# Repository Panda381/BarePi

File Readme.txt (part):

BarePi - Modular microchip kit
==============================
Last Update: 07/18/2026
Copyright (c) 2026 Miroslav Nemecek

Panda38@seznam.cz
hardyplotter2@gmail.com
https://github.com/Panda381/BarePi
https://www.breatharian.eu/hw/barepi/index_en.html

Note: The schematics and PCBs are in KiCAD version 9 format. The PCBs were
originally designed for home production using photolithography and may not be
properly prepared for professional production. If you want to have your PCBs
professionally produced, I recommend checking the designs carefully, especially
the dimensions of the components, which may not be correctly defined.
Typically, SMD capacitors may not have the correct dimensions.

Note 2: A WCH-LinkE programmer (available e.g. here
https://pajenicko.cz/usb-programator-a-debug-adapter-wch-link) may be required
to program CH32xxx processors. Before using it for the first time, it may be
necessary to upgrade the firmware of the programmer first - this can be done in
the MounRiver Studio development environment.

License
-------
All of my software creations are distributed under the Unlicense
https://spdx.org/licenses/Unlicense.html,
and my hardware creations under the CC0 license
https://creativecommons.org/publicdomain/zero/1.0/legalcode.en.
You are free to use, modify, and distribute them for any purpose without having
to credit me as the author. The exception is content derived from third-party
sources. These third-party components are not covered by my Unlicense or CC0
licenses, but rather by the original license terms of their authors. These
components are marked in the code, and when using them, you must comply with
the terms of the original licenses.

Contents
--------
- Description of the kit (basic characteristics of the kit)
- Bus connector (description of signals on the bus connector)
- Display connector (description of signals on the display connector)
- ZeroTiny (example of a minimalist game console with a Raspberry Zero module,
  created based on kit modules)
- EEPROM and driver formats (structure of EEPROMs and Register-Controlled
  Drivers)

Special modules
- Base (basic module - USB power supply, 3.3V stabilizer, audio output, microSD
  card, Reset button)
- BusExp (bus expander for connecting 4 modules)
- Port (ports SPI, I2C, UART, digital I/O, ADC)
- RTC (real-time clock and EEPROM memory)
- TestLed (bus tester)

Processors
- MegaTinyJoypad (Mega Tiny Joypad game console, ESP-07S processor module,
  128x64 OLED display)
- PGA2350 (PicoPadPGA game console, RP2350 processor)
- PicoPad (PicoPad console, RP2040 or RP2350 processor)
- PicoPadHSTX (PicoPadHSTX console with VGA or HDMI output, RP2350 processor)
- PidiBoy (PidiBoy console, CH32V006F8P6 processor, 128x64 OLED display)
- PidiMet, PidiMetAdapter (universal multimeter)
- PidiPad (PidiPad console, CH32V006E8R6 processor, output to VGA monitor)
- SumoPad (SumoPad console, CH32V208RBT6 processor, output to VGA monitor or
  LCD display 320x240)
- TinyJoypad (Tiny Joypad game console, ATtiny85 processor, 128x64 OLED
  display)
- TweetyBoy (TweetyBoy game console, CH32X035G8R6 processor, 160x80 LCD
  display)
- Zero (Raspberry Zero 1 or Raspberry Zero 2 module)

Displays
- DispHDMI (adapter for connecting an HDMI monitor)
- DispVGA (adapter for connecting a VGA monitor)
- ExtDisp (converter for grabbing a 320x240 LCD display and displaying it on a
  VGA or HDMI monitor)
- LCD16x2 (text LCD display, 2 rows of 16 characters)
- LCD160x80 (LCD color display 160x80)
- LCD320x240 (LCD color display 320x240)
- LED12 (7-segment LED display with 12 positions)
- OLED128x64 (OLED black and white display 128x64)

Keyboard
- CalcKey (calculator keyboard)
- KeyPad (basic gaming keyboard with 9 buttons)
- MiniKey (minimalist alphanumeric keyboard)

Description of the kit
----------------------
BarePi is a modular microchip kit designed for programming small devices such
as game consoles or calculators. The main focus is on the Raspberry Zero 2
module, programmed as bare-metal (i.e. without an operating system) with
library PiLibSDK (link www https://www.breatharian.eu/hw/pilibsdk/index_en.html,
GitHub https://github.com/Panda381/PiLibSDK). However, other types of
processors supporting 3.3V signals can also be used (ATmega, CH32V, ESP32).
The modules of the kit are connected via 40-pin connectors, forming a bus with
signals defined according to the Raspberry Zero 2 module. The connectors
ensure sufficient connection strength, no additional mechanical connections
are needed. Most modules are pass-through - they contain both a bus input
connector on the top edge of the board and a bus output connector on the
bottom edge of the board. The exceptions are the processor modules, which
contain only an output connector, and the alphanumeric keyboard module, which
has only an input connector.

The connection connector consists of a 2x20-pin female header on the bottom of
the module (signal output from the module - e.g. processor module) and a
2x20-pin pin header on the top of the module (signal input to the module - e.g.
keyboard). Most modules have a width of 65 millimeters, based on the width of
the Raspberry Zero 2 module. Most devices contain a processor module, a "Base"
module with power supply and sound output, a display module and a keyboard
module. All signals on the bus are at 3.3V levels. The bus also contains a 5V
supply voltage, but this voltage is used both to supply power to the device
(followed by a 3.3V stabilizer) and as a voltage for a possible signal
converter to the 5V level. The 5V level must not be applied to the signal wires
themselves, in many cases this could damage the device.

When building modules, you can solder the processor and display modules hard
over the pin strip, but I recommend using a socket strip for easy replacement.
The kit modules can be used in the simplest form, just the printed circuit
board itself, but it is more luxurious to add a top panel. For some modules,
such as the keyboard, the top panel is necessary because of the key labels. An
additional printed circuit board can be used as the top panel, screwed to the
module using spacers. The materials also include graphics for the bottom panel,
but it is probably unnecessary - the bottom side of the module can be treated,
for example, by gluing foam strips from window insulation so that the bottom
side of the printed circuit board does not scratch the table. For the kit
prototypes, instead of the top panel, I used only printed cardboard paper,
covered with insulating tape against abrasion and with holes punched with a
leather punch. For keyboards, I recommend adjusting the height of the keys so
that the keycaps protrude 1 mm above the surface of the top panel. If the
protrusion is too large, the keys may press into your fingers when pressed, and
if the protrusion is too small, more force may be required to press.

Bus connector
-------------
Definition of the signals on the bus connector, looking at the header strip on
the bottom edge of the module. The corresponding GPIO pin number of the
Raspberry Zero 2 module is shown in parentheses.

1,2 5V ... Supply voltage 5V. It is used to power the device, e.g. from a USB
connector or a 3.7V battery. The device itself is powered by a voltage of 3.3V,
so the device must also include a voltage stabilizer for 3.3V. All signals on
the bus are at 3.3V levels. If signals with a 5V level are needed, a level
converter must be used.

3,4 3V3 ... Supply voltage 3.3V. This is the main supply voltage of the device.
It can be obtained by a stabilizer from a 5V voltage (e.g. from a USB
connector) or a voltage converter from a battery.

5 BUS_SDA (GPIO0) ... Internal I2C bus data wire. The internal I2C bus is used
to directly control the modules of the kit. The internal I2C bus can be a
separate bus, separated from the external user I2C bus, so that the user can
independently control the communication. In the Raspberry Zero 2 module, this
is the I2C0 bus. In other modules, the internal I2C bus can be shared with the
external I2C bus. In the Raspberry Zero 2 module, the I2C0 bus is also used to
access the system ID EEPROM memory when the device is turned on - this must be
remembered to avoid overlapping the functions of the EEPROM memory. The signal
is of the open collector type - pull-up resistors must be used.

6 BUS_SCL (GPIO1) ... Clock wire of the internal I2C bus. In the Raspberry
Zero 2 module this is the I2C0 bus. The signal is of the open collector type -
pull-up resistors must be used.

7 I2C_SDA (GPIO2) ... External I2C bus data wire. The external I2C bus is used
to control user devices so that communication does not conflict with the
control of the kit modules. In the Raspberry Zero 2 module, this is the I2C1
bus. In other modules, the external I2C bus may be shared with the internal I2C
bus. The signal is of the open collector type - pull-up resistors must be used.

8 I2C_SCL (GPIO3) ... Clock wire of external I2C bus. In Raspberry Zero 2
module this is I2C1 bus. Signal is open collector type - pull-up resistors must
be used.

9 KEY_ALT (GPIO4) ... Input of the alternative function button "ALT". The
button changes the meaning of the other keyboard keys. The button connects the
pin to GND and requires the use of a pull-up resistor. This signal can also
have other functions if the button function is not used. The clock signal from
the processor can be output to the pin - in the Raspberry Zero 2 module this is
the GPCLK0 signal. For this reason, the "ALT" button should be connected via a
protective resistor (e.g. 1K0), which will prevent damage to the circuits if
the button is accidentally pressed if the clock signal is output to the pin.
Another additional function of the pin is the input of the ADC converter -
typically in the Raspberry Pico and CH32 modules.

10 KEY_DOWN (GPIO5) ... "DOWN" button input. Along with the "ALT" button, it
has an alternative meaning of "Page Down". The button connects the pin to GND
and requires the use of a pull-up resistor.

11 KEY_UP (GPIO6) ... "UP" button input. Along with the "ALT" button, it has an
alternative meaning of "Page Up". The button connects the pin to GND and
requires the use of a pull-up resistor.

12 SPI_CS1 (GPIO7) ... The second SPI bus select signal. In the Raspberry Zero
module, this is the SPI0 bus.

13 SPI_CS0 (GPIO8) ... The first SPI bus select signal. In the Raspberry Zero
module, this is the SPI0 bus.

14 SPI_MISO (GPIO9) ... SPI bus MISO signal - data input to the processor from
the peripheral (RX signal). In the Raspberry Zero module, this is the SPI0 bus.
In some devices, the SPI bus may be shared with the SD card - in this case, it
is necessary to remove the SD card from the slot before using the SPI bus.

15 SPI_MOSI (GPIO10) ... SPI bus MOSI signal - data output from the processor
to the peripheral (TX signal). In the Raspberry Zero module, this is the SPI0
bus.

16 SPI_SCLK (GPIO11) ... SPI bus clock signal. In the Raspberry Zero module,
this is the SPI0 bus.

17 PWM_L (GPIO12) ... Left channel audio output. Typically PWM modulation, so
an RC filter may be required.

18 PWM_R (GPIO13) ... Right channel audio output. Typically PWM modulation, so
an RC filter may be required.

19 UART_TX (GPIO14) ... Serial data output of the UART port. In some modules,
this pin can be used as a CAN Bus serial data output (CAN_TX signal).

20 UART_RX (GPIO15) ... Serial data input of the UART port. In some modules,
this pin can be used as a CAN Bus serial data input (CAN_RX signal).

21 LCD_DC (GPIO16) ... Control signal for LCD SPI display - resolution of data
and control code.

22 LCD_RES (GPIO17) ... Signal to reset the LCD SPI display controller.

23 LCD_CS (GPIO18) ... Signal for selecting the LCD SPI display. In the
Raspberry Zero module, this is the SPI1 bus. The PCM_CLK signal for the I2S/PCM
interface can optionally be available on this pin.

24 LCD_BL (GPIO19) ... Signal for controlling the brightness of the LCD SPI
display backlight. Typically, this is a PWM signal. Optionally, the PCM_FS
signal for the I2S/PCM interface can be available on this pin. If the processor
does not allow smooth brightness control, this pin should be HIGH for full
display brightness.

25 LCD_MOSI (GPIO20) ... Serial data output to the LCD SPI display. In the
Raspberry Zero module, this is the SPI1 bus. The PCM_DIN signal for the I2S/PCM
interface can optionally be available on this pin.

26 LCD_SCK (GPIO21) ... LCD SPI display clock signal. In the Raspberry Zero
module, this is the SPI1 bus. Optionally, the PCM_DOUT signal for the I2S/PCM
interface can be available on this pin.

27 KEY_A (GPIO22) ... Input button "A" - the main action button. On the
alphanumeric keyboard, it corresponds to the "Spacebar" key. Together with the
"ALT" button, it has an alternative meaning of "Zoom" - switching the view on
the built-in LCD display. The button connects the pin to GND and requires the
use of a pull-up resistor.

28 KEY_B (GPIO23) ... "B" button input - secondary action button. On an
alphanumeric keyboard, it corresponds to the "Enter" key. Together with the
"ALT" button, it has an alternative meaning of "Insert". The button connects
the pin to GND and requires the use of a pull-up resistor.

29 KEY_X (GPIO24) ... Input button "X" - additional functions button (e.g.
help). On the alphanumeric keyboard it corresponds to the "Tab" key. Together
with the "ALT" button it has an alternative meaning "Print Screen" - screenshot
of the screen contents to a file. The button connects the pin to GND and
requires the use of a pull-up resistor.

30 KEY_RIGHT (GPIO25) ... "RIGHT" button input. Along with the "ALT" button, it
has an alternative meaning of "End". The button connects the pin to GND and
requires the use of a pull-up resistor.

31 KEY_LEFT (GPIO26) ... "LEFT" button input. Along with the "ALT" button, it
has an alternative meaning of "Home". The button connects the pin to GND and
requires the use of a pull-up resistor.

32 KEY_Y (GPIO27) ... "Y" button input - interrupt, exit or menu button. On an
alphanumeric keyboard, it corresponds to the "Esc" key. Together with the "ALT"
button, it has an alternative meaning of "Menu", invoking the system menu. The
button connects the pin to GND and requires the use of a pull-up resistor.

33 SD_CS ... SPI signal for selecting the SD card. An LED indicating access to
the SD card can be connected to this signal.

34 SD_MISO ... SPI data input from SD card to processor.

35 SD_MOSI ... SPI data output from the processor to the SD card.

36 SD_SCLK ... SPI clock for SD card.

37 USR_LED ... Output to user LED. Active signal is HIGH.

38 RESET ... "RESET" button input for resetting the processor. The button
connects the pin to GND and requires the use of a pull-up resistor. For some
modules, the pull-up resistor is internally part of the module.

39, 40 GND ... Ground 0V.

In most modules, the I2C bus signals are equipped with a 15K pull-up resistor.
This value should ensure reliable bus operation with 1 to 5 connected devices.
The BarePi kit modules use the following I2C addresses:
0x30 ... LCD SPI graphics display (LCD320x240, LCD160x80)
0x31 ... LCD text display (LCD16x2)
0x32 ... LED 7-segment display (LED12)
0x34 ... alphanumeric keyboard (MiniKey)
0x35 ... calculator keyboard (CalcKey)
0x38 ... PORT interface (Port module)
0x3C ... OLED display SSD1306
0x50-0x56 ... EEPROMs
0x57 ... configuration EEPROM 4KB AT24C32
0x68 ... RTC clock DS3231

Display connector
-----------------
Some modules allow image output to an external display with a VGA or HDMI
interface. These modules contain a 2x10-pin female header connector that
contains signals for output to both an HDMI display and a VGA display. In
addition, the connector contains a signal used to detect whether a DispHDMI,
DispVGA module is inserted into the connector or the connector is left free.
Accordingly, the interface for an HDMI display, a VGA display or an internal
LCD display can be selected.

Definition of the signals on the display connector, looking at the female
header strip at the output of the processor module. The corresponding GPIO pin
number of the PGA2350 module is shown in parentheses.

1 HSYNC (GPIO18) ... Horizontal synchronization of the VGA display. The signal
is protected in the DispVGA adapter by the 47 ohm resistor to limit current
surge on long wires.

2 VSYNC (GPIO19) ... Vertical synchronization of the VGA display. The signal is
protected in the DispVGA adapter by the 47 ohm resistor to limit current surge
on long wires.

3 GND ... Ground 0V.

4 BLUE ... Blue color component for VGA display.

5 DISP_SEL ... Detection of connected adapter. The signal is connected to GND
in the DispVGA adapter, to 3V3 in the DispHDMI adapter. If no adapter is
inserted, the signal is not connected to any wire - in this configuration, an
internal LCD display can be used. In some devices, in this third state,
autodetection of the connected VGA or HDMI monitor type is performed - by
testing the impedance on the VGA connector. However, it is not recommended to
use autodetection, as it is not reliable enough.

6 GREEN ... Green color component for VGA display.

7 3V3 ... Supply voltage 3.3V. Reserved for pull-up resistors of the DispHDMI
adapter, currently not used.

8 RED ... Red color component for VGA display.

9 HOTPLUG ... HDMI monitor connection detection. If an HDMI monitor is
connected and ready to receive a signal, it sets the HOTPLUG signal to HIGH.
During normal operation, the device will only start transmitting the image when
the HOTPLUG signal is set. The signal is usually +5V, so a resistor divider is
used in the DispHDMI adapter to reduce the voltage to 3.3V. Currently, no
modules in the kit use the HOTPLUG signal; the image is transmitted
independently of the monitor connection.

10 5V ... Supply voltage 5V. The voltage is used to power the monitor's
communication circuits, to power display adapters (e.g. VGA to HDMI converter)
and to power the monitor's configuration EEPROM. The current is limited by a 47
ohm protective resistor in the adapters.

11 SDA ... I2C bus data signal used to read EDID data from an HDMI monitor.
Currently, no kit modules use this signal. Be careful when using it - on most
monitors the signal is connected via a pull-up resistor to +5V, which can be
dangerous for circuits operating at 3.3V levels.

12 SCL ... I2C bus clock signal used to read EDID data from HDMI monitor.
Currently, no kit modules use this signal. Be careful when using it - on most
monitors the signal is connected via a pull-up resistor to +5V, which can be
dangerous for circuits operating with 3.3V levels.

13 CKN (GPIO15) ... CK- signal for HDMI display. The signal is limited by a 270
ohm resistor in the HDMI adapter.

14 CKP (GPIO14) ... CK+ signal for HDMI display. The signal is limited by a 270
ohm resistor in the HDMI adapter.

15 D0N (GPIO13) ... D0- signal for HDMI display. The signal is limited by a 270
ohm resistor in the HDMI adapter.

16 D0P (GPIO12) ... D0+ signal for HDMI display. The signal is limited by a 270
ohm resistor in the HDMI adapter.

17 D1N (GPIO19) ... D1- signal for HDMI display. The signal is limited by a 270
ohm resistor in the HDMI adapter.

18 D1P (GPIO18) ... D1+ signal for HDMI display. The signal is limited by a 270
ohm resistor in the HDMI adapter.

19 D2N (GPIO17) ... D2- signal for HDMI display. The signal is limited by a 270
ohm resistor in the HDMI adapter.

20 D2P (GPIO16) ... D2+ signal for HDMI display. The signal is limited by a 270
ohm resistor in the HDMI adapter.

EEPROM and Driver Formats
-------------------------
The BarePi kit uses a uniform structure in its EEPROM configuration memories
and register-controlled devices, facilitating access to data and control
registers. The EEPROMs used in the BarePi kit, as well as the module
controllers, are controlled via the I2C bus, typically operating at 100 kHz.
The module controllers typically contain a CH32V-series processor, which is
accessible via the I2C bus in a manner similar to EEPROM memory with 8-bit or
16-bit addressing. At the beginning of the memory space are the controller's
control and data registers, followed by the processor's Flash memory, which
can be used similarly to EEPROM memory to store configuration information.
However, it is important to note that the processor's Flash memory has a more
limited number of write cycles than EEPROM memory - typically several thousand
write cycles.

Memories ranging in size from 512 bytes to 64 KB are addressed using a 16-bit
address. Memories of 256 bytes or less are addressed using an 8-bit address.
This differs from traditional EEPROMs - memory blocks ranging from 512 bytes to
2 KB are typically originally addressed as 256-byte blocks across multiple I2C
addresses. In BarePi, all memory blocks are addressed using a single I2C
address, either in 8-bit or 16-bit mode, depending on their size. While the
original 512B - 2KB EEPROMs can also be used, they can only be configured as
multiple 256B memory blocks at multiple addresses.

To access the devices, I recommend using only the 100 kHz I2C speed. Higher
speeds may be too much for the processors in the modules to handle reliably.
The 16-bit memory cell address is in big-endian format (Motorola format),
similar to the EEPROM memory address - that is, the high byte of the address is
transmitted first, followed by the low byte. However, the data in the memories
is in little-endian format (Intel format) - that is, the lower byte comes
first, and at higher addresses, the higher byte comes first. Additionally, I
recommend maintaining the alignment of entries (e.g., aligning a 16-bit word to
an even address) so that the control processor can more easily access the
record entries in its structures.

At the beginning of the EEPROM configuration memory and the device memory,
there is a 4-byte header with identification:

- Memory offset 0: "BPi" ... 3 characters containing the magic text "BPi"
  (= "Bare Pi")

- Memory offset 3: "D" ... a character representing the total memory size:
  ('3'=8B, ... '9'=512B, 'A'=1KB, ... 'G'=64KB). This character can be used by
  the main processor to detect the memory size - but only in 16-bit mode,
  meaning memory sizes ranging from 512B to 64KB. Smaller memory sizes cannot
  be detected because 8-bit and 16-bit access modes cannot be mixed.

Configuration records begin at memory offset 4. Each record begins with a
4-byte header:

- Record offset 0: ... 2 bytes containing the record type identifier, in
  little-endian format (the lower byte is at the lower address). Values from
  0x0001 to 0x00FF are reserved for internal use by the BarePi kit. The value
  0x0001 denotes the device controller's register array. The value 0x0002
  indicates the device's freely usable RAM. The value 0xFFFF indicates the end
  of records - before memory formatting, the memory is initialized to 0xFF and
  the header is written; the bytes 0xFF 0xFF following the header indicate the
  end of the record array.

- Record offset 2: ... 2 bytes containing the length of the following data
  (excluding the header).

The PiLisbSDK library for the Raspberry Zero 1/2 module includes the
"drv_i2cbus.*" driver for easy access to memory and devices, enabling simple
communication with devices on the I2C bus via a message queue. The
"drv_eeprom.*" driver is available for easy use of entries in the configuration
memory.

ZeroTiny
--------
The game console "ZeroTiny" is not directly part of the BarePi kit. This is a
minimalist game console with a Raspberry Zero 2 or Raspberry Zero 1 module. It
is an example of creating an end device based on the modules of the kit. Its
connection corresponds to the connection of the "Zero", "Base" and "KeyPad"
modules. In the construction, I recommend using a female connector strip rather
than direct soldering of the Zero module - so that the Zero 1 or Zero 2 modules
can be exchanged. The ZeroTiny console in the PiLibSDK library, where you can
also find sample applications:
www https://www.breatharian.eu/hw/pilibsdk/index_en.html#zerotiny
GitHub https://github.com/Panda381/PiLibSDK

Special modules
===============

Base
----
The "Base" module is the basic module of the kit. The module can be used with
all devices - it provides power to the device from the USB connector (using a
3.3V stabilizer), audio output, microSD card slot, processor reset button, SD
card access LED and user LED. Before manufacturing the PCB, check the
definition for the audio connector, SD card slot, speaker and HT7533 stabilizer
- the coordinates and meaning of the pins may vary from manufacturer to
manufacturer. There is a jumper on the module that determines whether the
internal 3.3V stabilizer is used. If the processor module contains its own
stabilizer, it may be appropriate to turn off the stabilizer on the "Base"
module. When constructing this module, I would like to point out that some
components are too close together and are difficult to solder - it might be
better to rearrange the board slightly and also choose larger housings for the
capacitors. The speaker could also use some improvement - the sound is quiet,
so an amplifier might be needed.

The PWM_L and PWM_R audio signals terminate in this module and do not continue
beyond it. This is to minimize interference with the audio signal. If possible,
connect the "Base" module first, immediately after the processor module. Better
routing of the audio wires and more thorough shielding would likely improve the
audio signal quality as well.

BusExp
------
The "BusExp" module is a bus expander. It allows you to connect up to 4 modules
together if you prefer to organize the modules "on top of each other" rather
than "side by side".

Port
----
The "Port" module is a module for connecting external peripherals. It contains
connectors for SPI, I2C, UART connections, as well as a CH32V002A4M6 processor,
which provides 12 digital inputs/outputs and 6 analog ADC inputs. The processor
is connected to the I2C bus at address 0x38.

You can find the processor firmware in the CH32LibSDK library in folder
ch32\BAREPI\PORT12\ (GitHub:
 https://github.com/Panda381/CH32LibSDK/tree/main/ch32/BAREPI/PORT12 ).

In the PiLibSDK library, you'll find the device driver in drv_port12.* (GitHub:
 https://github.com/Panda381/PiLibSDK/tree/main/_drv ).

In the PiLibSDK library, you'll find the test program in Apps\TEST\PORT2
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
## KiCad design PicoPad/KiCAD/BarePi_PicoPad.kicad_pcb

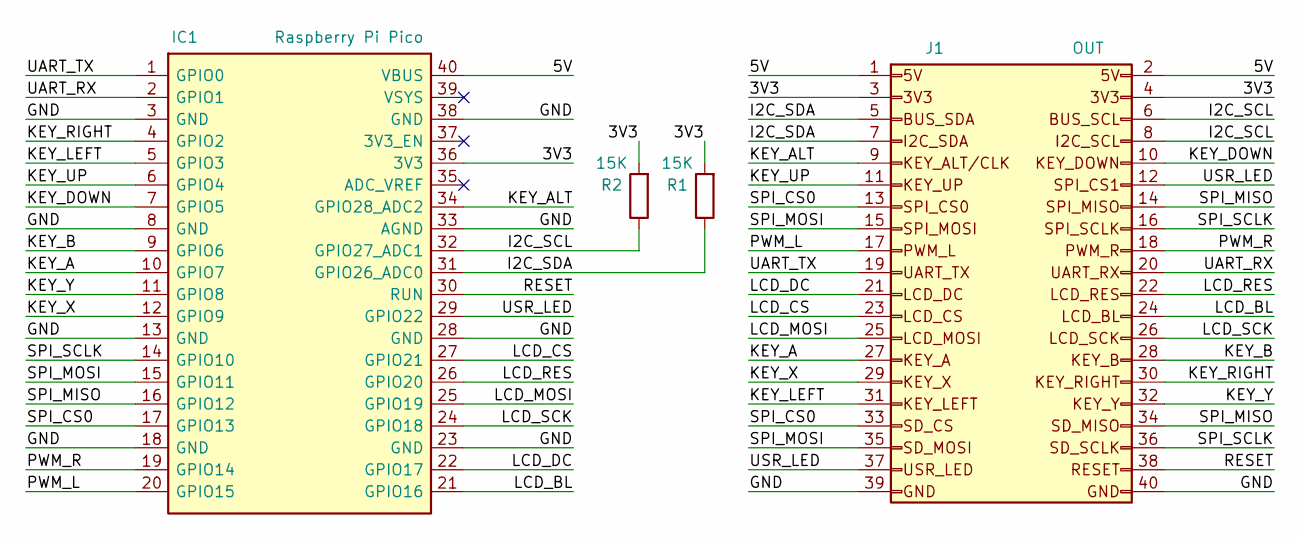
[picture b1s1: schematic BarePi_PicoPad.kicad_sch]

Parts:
IC1: Raspberry Pi Pico; Raspberry_Pi_Pico_Common_Unspecified
J1: OUT; Raspberry_OUT_PinSocket_2x20_P2.54mm_Horizontal
R1, R2: 15K; R_1206_3216Metric_Pad1.30x1.75mm_HandSolder

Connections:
/3V3: IC1.36 (3V3), J1.3, J1.4, R1.2, R2.2
/5V: IC1.40 (VBUS), J1.1, J1.2
/GND: IC1.3 (GND), IC1.8 (GND), IC1.13 (GND), IC1.18 (GND), IC1.23 (GND), IC1.28 (GND), IC1.33 (AGND), IC1.38 (GND), J1.39, J1.40
/I2C_SCL: IC1.32 (GPIO27_ADC1), J1.6, J1.8, R2.1
/I2C_SDA: IC1.31 (GPIO26_ADC0), J1.5, J1.7, R1.1
/KEY_A: IC1.10 (GPIO7), J1.27
/KEY_ALT: IC1.34 (GPIO28_ADC2), J1.9
/KEY_B: IC1.9 (GPIO6), J1.28
/KEY_DOWN: IC1.7 (GPIO5), J1.10
/KEY_LEFT: IC1.5 (GPIO3), J1.31
/KEY_RIGHT: IC1.4 (GPIO2), J1.30
/KEY_UP: IC1.6 (GPIO4), J1.11
/KEY_X: IC1.12 (GPIO9), J1.29
/KEY_Y: IC1.11 (GPIO8), J1.32
/LCD_BL: IC1.21 (GPIO16), J1.24
/LCD_CS: IC1.27 (GPIO21), J1.23
/LCD_DC: IC1.22 (GPIO17), J1.21
/LCD_MOSI: IC1.25 (GPIO19), J1.25
/LCD_RES: IC1.26 (GPIO20), J1.22
/LCD_SCK: IC1.24 (GPIO18), J1.26
/PWM_L: IC1.20 (GPIO15), J1.17
/PWM_R: IC1.19 (GPIO14), J1.18
/RESET: IC1.30 (RUN), J1.38
/SPI_CS0: IC1.17 (GPIO13), J1.13, J1.33
/SPI_MISO: IC1.16 (GPIO12), J1.14, J1.34
/SPI_MOSI: IC1.15 (GPIO11), J1.15, J1.35
/SPI_SCLK: IC1.14 (GPIO10), J1.16, J1.36
/UART_RX: IC1.2 (GPIO1), J1.20
/UART_TX: IC1.1 (GPIO0), J1.19
/USR_LED: IC1.29 (GPIO22), J1.12, J1.37

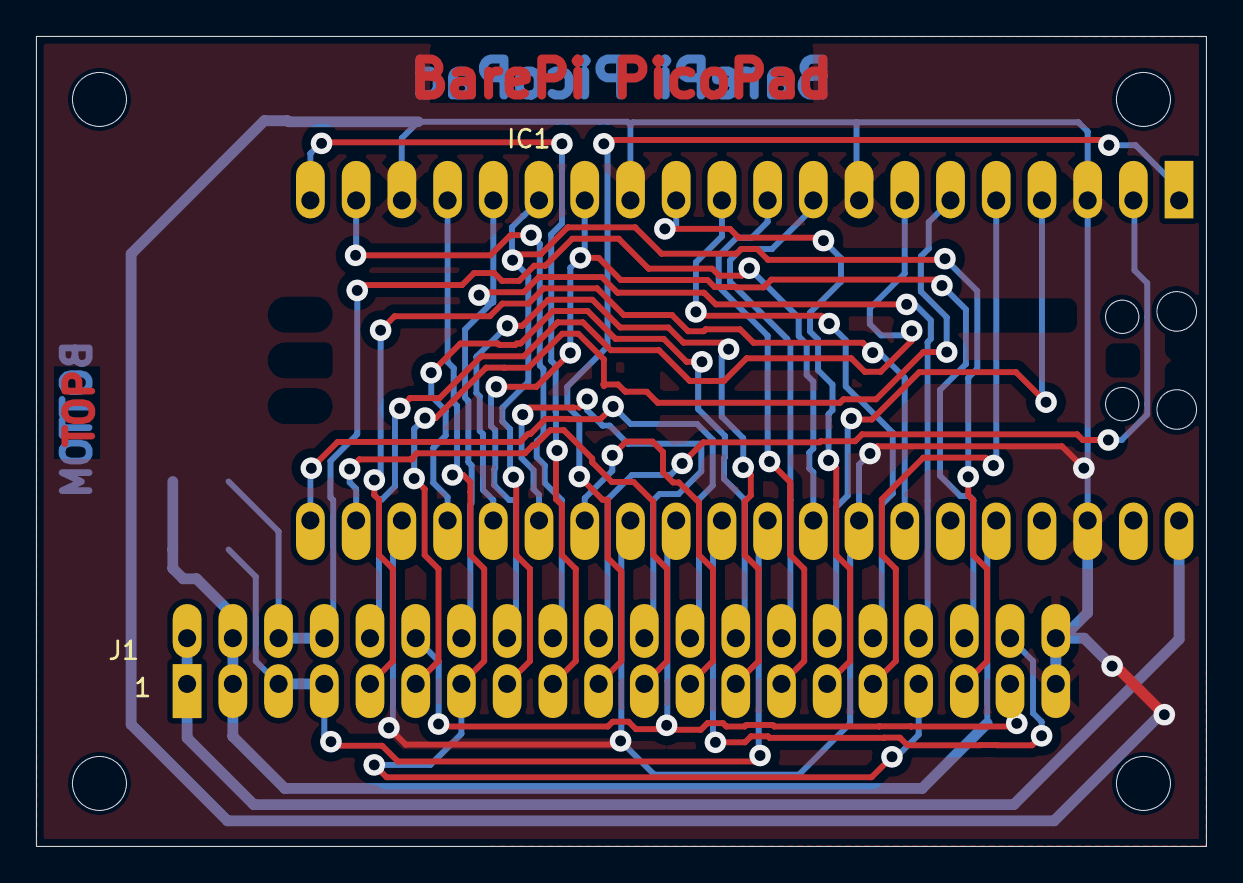
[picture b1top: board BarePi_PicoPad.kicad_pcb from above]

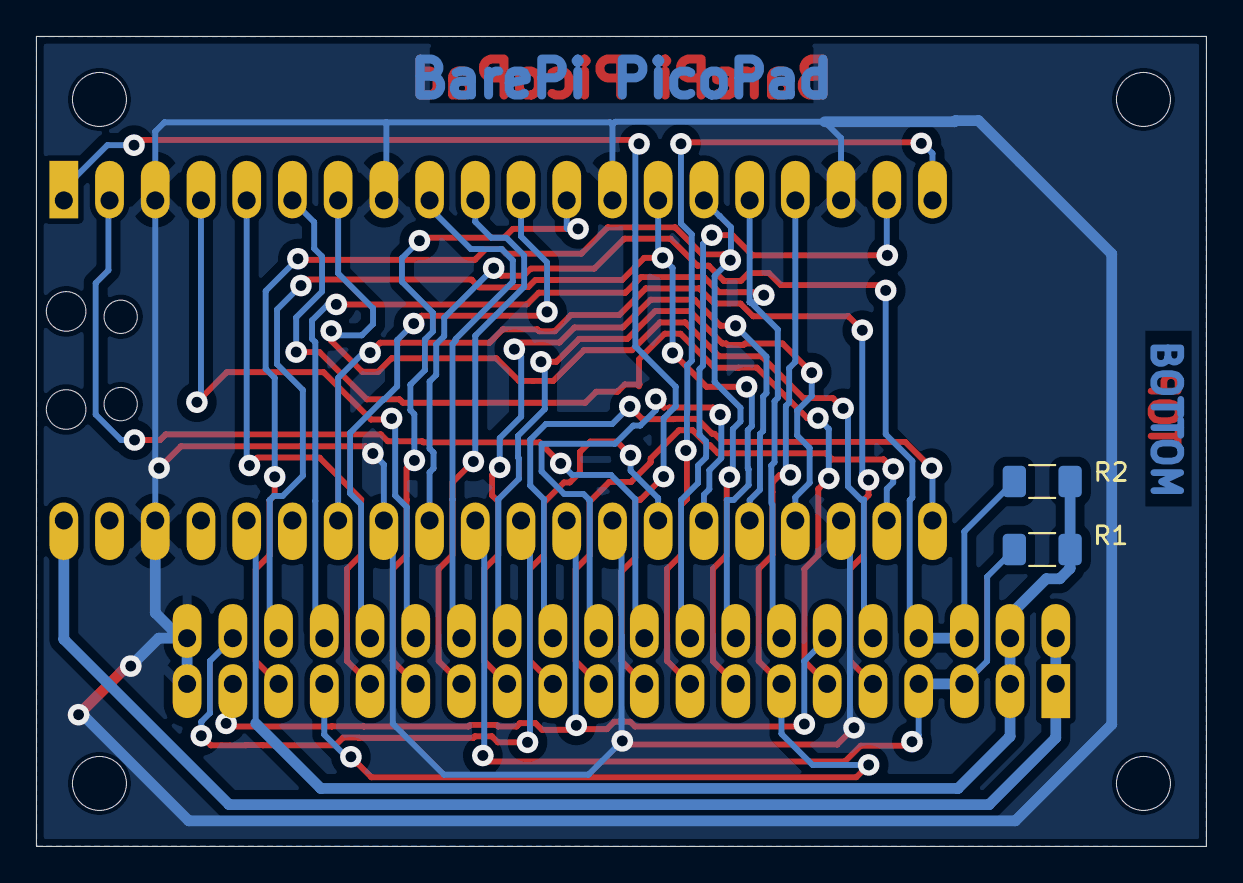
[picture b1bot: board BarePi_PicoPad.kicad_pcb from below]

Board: 2 copper layers, 65.0 x 45.0 mm, 4 parts (2 on the bottom side), 30 nets.

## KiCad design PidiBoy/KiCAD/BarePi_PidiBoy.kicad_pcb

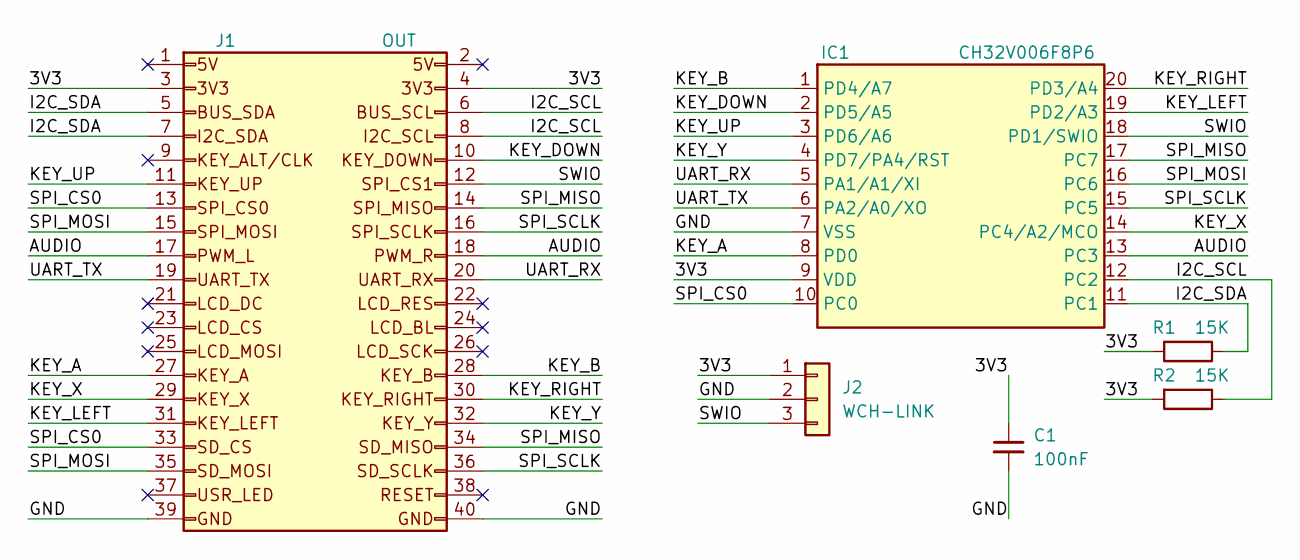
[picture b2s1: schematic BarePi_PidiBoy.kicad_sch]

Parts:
C1: 100nF; C_1206_3216Metric_Pad1.33x1.80mm_HandSolder
IC1: CH32V006F8P6; Raspberry_TSSOP-20_4.4x6.5mm_P0.65mm
J1: OUT; Raspberry_OUT_PinSocket_2x20_P2.54mm_Horizontal
J2: WCH-LINK; Raspberry_PinHeader_1x03_P2.54mm_Horizontal
R1, R2: 15K; R_1206_3216Metric_Pad1.30x1.75mm_HandSolder

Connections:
/3V3: C1.1, IC1.9 (VDD), J1.3, J1.4, J2.1, R1.2, R2.2
/AUDIO: IC1.13 (PC3), J1.17, J1.18
/GND: C1.2, IC1.7 (VSS), J1.39, J1.40, J2.2
/I2C_SCL: IC1.12 (PC2), J1.6, J1.8, R2.1
/I2C_SDA: IC1.11 (PC1), J1.5, J1.7, R1.1
/KEY_A: IC1.8 (PD0), J1.27
/KEY_B: IC1.1 (PD4/A7), J1.28
/KEY_DOWN: IC1.2 (PD5/A5), J1.10
/KEY_LEFT: IC1.19 (PD2/A3), J1.31
/KEY_RIGHT: IC1.20 (PD3/A4), J1.30
/KEY_UP: IC1.3 (PD6/A6), J1.11
/KEY_X: IC1.14 (PC4/A2/MCO), J1.29
/KEY_Y: IC1.4 (PD7/PA4/RST), J1.32
/SPI_CS0: IC1.10 (PC0), J1.13, J1.33
/SPI_MISO: IC1.17 (PC7), J1.14, J1.34
/SPI_MOSI: IC1.16 (PC6), J1.15, J1.35
/SPI_SCLK: IC1.15 (PC5), J1.16, J1.36
/SWIO: IC1.18 (PD1/SWIO), J1.12, J2.3
/UART_RX: IC1.5 (PA1/A1/XI), J1.20
/UART_TX: IC1.6 (PA2/A0/XO), J1.19

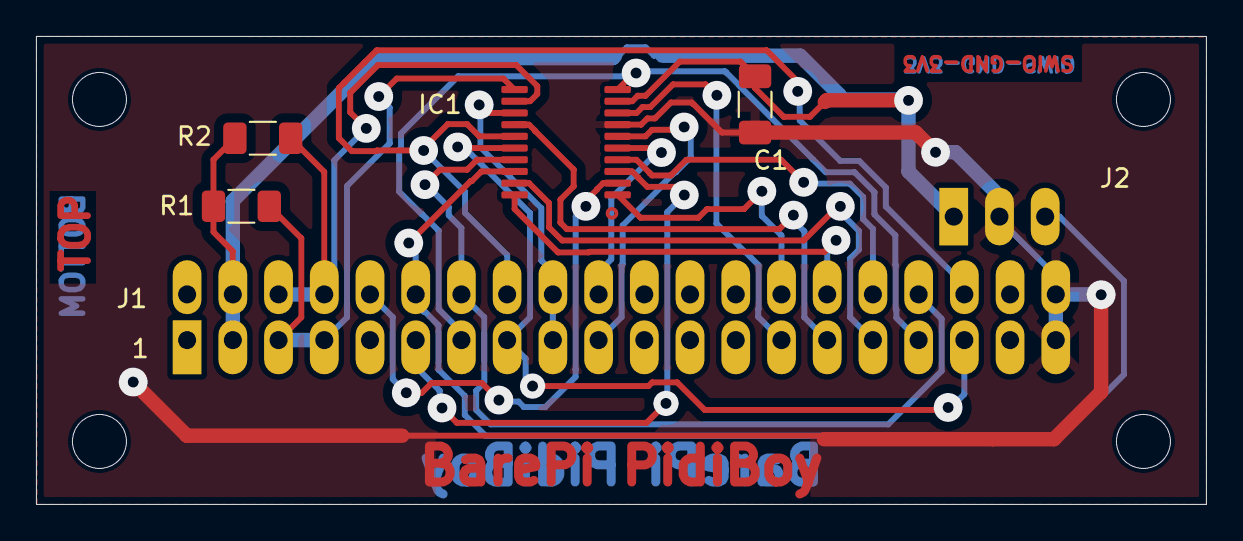
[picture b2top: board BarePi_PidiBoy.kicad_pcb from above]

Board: 2 copper layers, 65.0 x 26.0 mm, 6 parts (0 on the bottom side), 20 nets.

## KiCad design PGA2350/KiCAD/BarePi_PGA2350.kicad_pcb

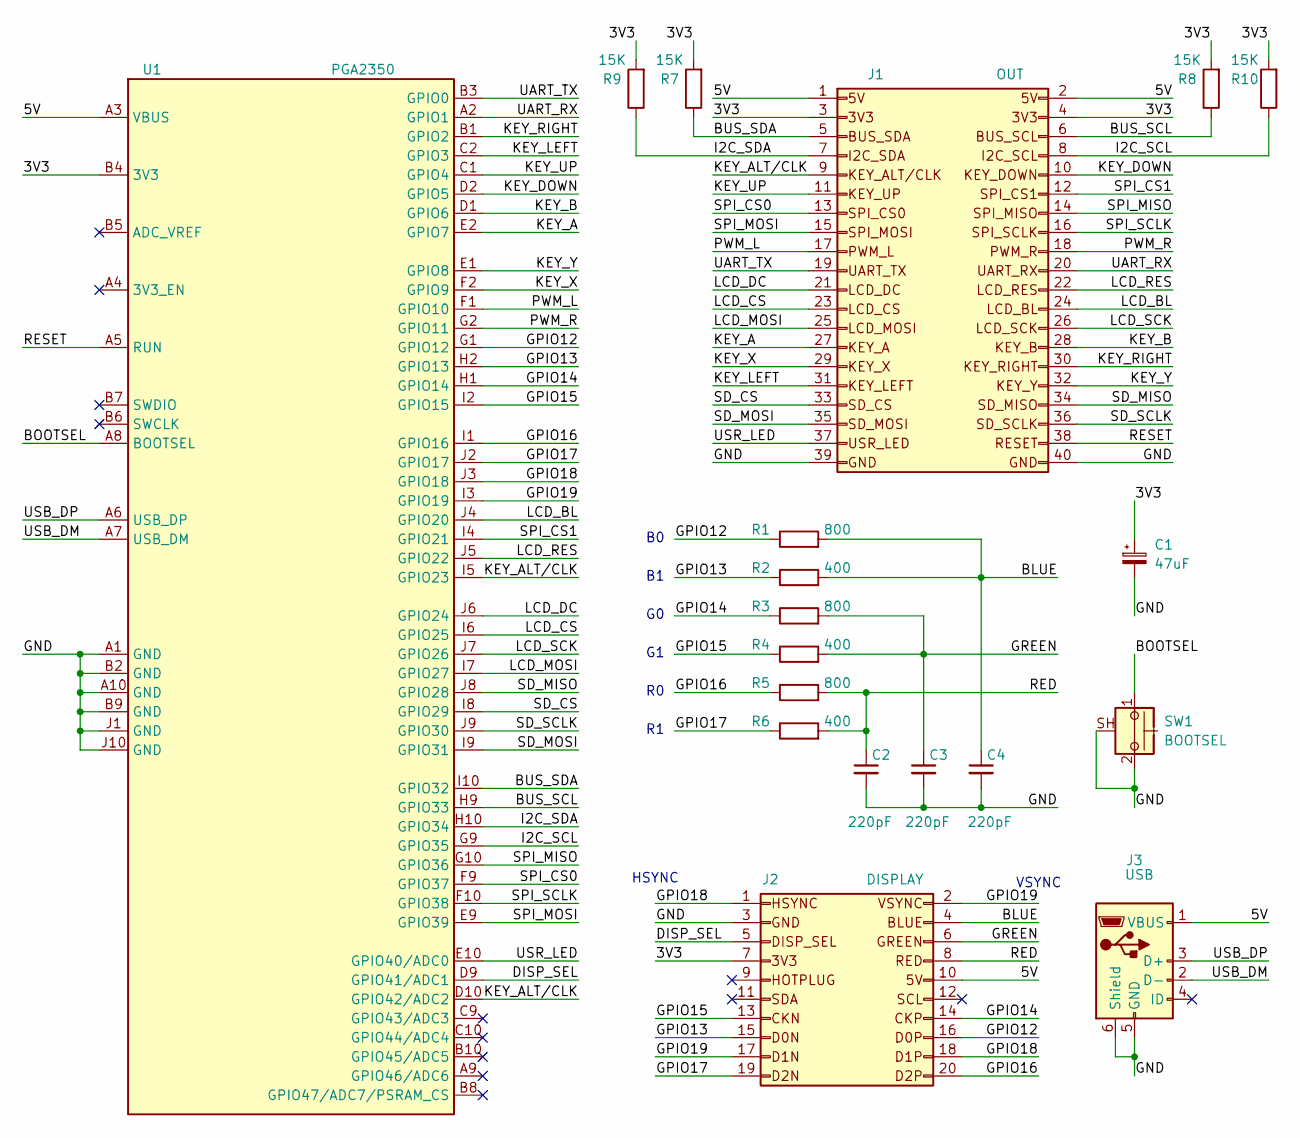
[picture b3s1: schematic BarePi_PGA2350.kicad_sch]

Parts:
C1: 47uF; CP_EIA-3216-18_Kemet-A_HandSolder
C2, C3, C4: 220pF; C_1206_3216Metric_Pad1.33x1.80mm_HandSolder
J1: OUT; Raspberry_OUT_PinSocket_2x20_P2.54mm_Horizontal
J2: DISPLAY; Raspberry_OUT_PinSocket_2x10_P2.54mm_Horizontal
J3: USB; Raspberry_USB_Micro-B_Amphenol_10104110_Horizontal
R1, R3, R5: 800; R_0805_2012Metric_Pad1.20x1.40mm_HandSolder
R2, R4, R6: 400; R_0805_2012Metric_Pad1.20x1.40mm_HandSolder
R7, R8, R9, R10: 15K; R_1206_3216Metric_Pad1.30x1.75mm_HandSolder
SW1: BOOTSEL; Raspberry_SW_SPST_Omron_B3F-315x_Angled
U1: PGA2350

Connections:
/3V3: C1.1, J1.3, J1.4, J2.7, R7.2, R8.2, R9.2, R10.2, U1.B4 (3V3)
/5V: J1.1, J1.2, J2.10, J3.1 (VBUS), U1.A3 (VBUS)
/BLUE: C4.1, J2.4, R1.2, R2.2
/BOOTSEL: SW1.1, U1.A8 (BOOTSEL)
/BUS_SCL: J1.6, R8.1, U1.H9 (GPIO33)
/BUS_SDA: J1.5, R7.1, U1.I10 (GPIO32)
/DISP_SEL: J2.5, U1.D9 (GPIO41/ADC1)
/GND: C1.2, C2.2, C3.2, C4.2, J1.39, J1.40, J2.3, J3.5 (GND), J3.6 (Shield), SW1.2, SW1.SH (B), U1.A1 (GND), U1.A10 (GND), U1.B2 (GND), U1.B9 (GND), U1.J1 (GND), U1.J10 (GND)
/GPIO12: J2.16, R1.1, U1.G1 (GPIO12)
/GPIO13: J2.15, R2.1, U1.H2 (GPIO13)
/GPIO14: J2.14, R3.1, U1.H1 (GPIO14)
/GPIO15: J2.13, R4.1, U1.I2 (GPIO15)
/GPIO16: J2.20, R5.1, U1.I1 (GPIO16)
/GPIO17: J2.19, R6.1, U1.J2 (GPIO17)
/GPIO18: J2.1, J2.18, U1.J3 (GPIO18)
/GPIO19: J2.2, J2.17, U1.I3 (GPIO19)
/GREEN: C3.1, J2.6, R3.2, R4.2
/I2C_SCL: J1.8, R10.1, U1.G9 (GPIO35)
/I2C_SDA: J1.7, R9.1, U1.H10 (GPIO34)
/KEY_A: J1.27, U1.E2 (GPIO7)
/KEY_B: J1.28, U1.D1 (GPIO6)
/KEY_DOWN: J1.10, U1.D2 (GPIO5)
/KEY_LEFT: J1.31, U1.C2 (GPIO3)
/KEY_RIGHT: J1.30, U1.B1 (GPIO2)
/KEY_UP: J1.11, U1.C1 (GPIO4)
/KEY_X: J1.29, U1.F2 (GPIO9)
/KEY_Y: J1.32, U1.E1 (GPIO8)
/LCD_BL: J1.24, U1.J4 (GPIO20)
/LCD_CS: J1.23, U1.I6 (GPIO25)
/LCD_DC: J1.21, U1.J6 (GPIO24)
/LCD_MOSI: J1.25, U1.I7 (GPIO27)
/LCD_RES: J1.22, U1.J5 (GPIO22)
/LCD_SCK: J1.26, U1.J7 (GPIO26)
/PWM_L: J1.17, U1.F1 (GPIO10)
/PWM_R: J1.18, U1.G2 (GPIO11)
/RED: C2.1, J2.8, R5.2, R6.2
/RESET: J1.38, U1.A5 (RUN)
/SD_CS: J1.33, U1.I8 (GPIO29)
/SD_MISO: J1.34, U1.J8 (GPIO28)
/SD_MOSI: J1.35, U1.I9 (GPIO31)
/SD_SCLK: J1.36, U1.J9 (GPIO30)
/SPI_CS0: J1.13, U1.F9 (GPIO37)
/SPI_CS1: J1.12, U1.I4 (GPIO21)
/SPI_MISO: J1.14, U1.G10 (GPIO36)
/SPI_MOSI: J1.15, U1.E9 (GPIO39)
/SPI_SCLK: J1.16, U1.F10 (GPIO38)
/UART_RX: J1.20, U1.A2 (GPIO1)
/UART_TX: J1.19, U1.B3 (GPIO0)
/USB_DM: J3.2 (D-), U1.A7 (USB_DM)
/USB_DP: J3.3 (D+), U1.A6 (USB_DP)
/USR_LED: J1.37, U1.E10 (GPIO40/ADC0)

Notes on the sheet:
VSYNC
HSYNC

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
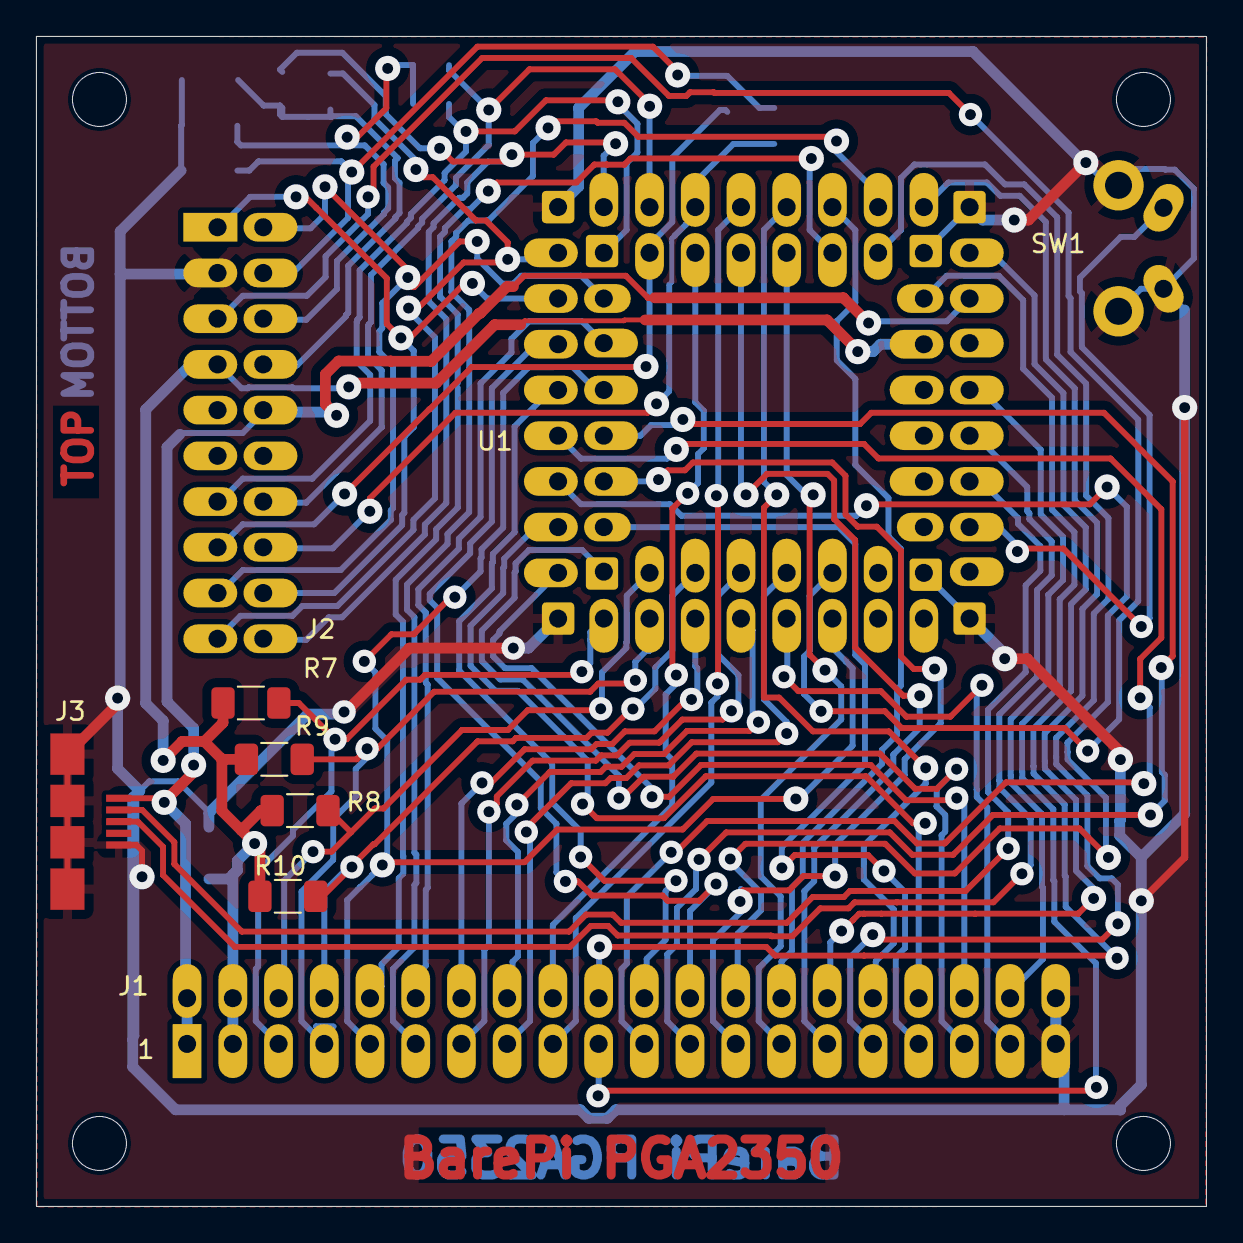
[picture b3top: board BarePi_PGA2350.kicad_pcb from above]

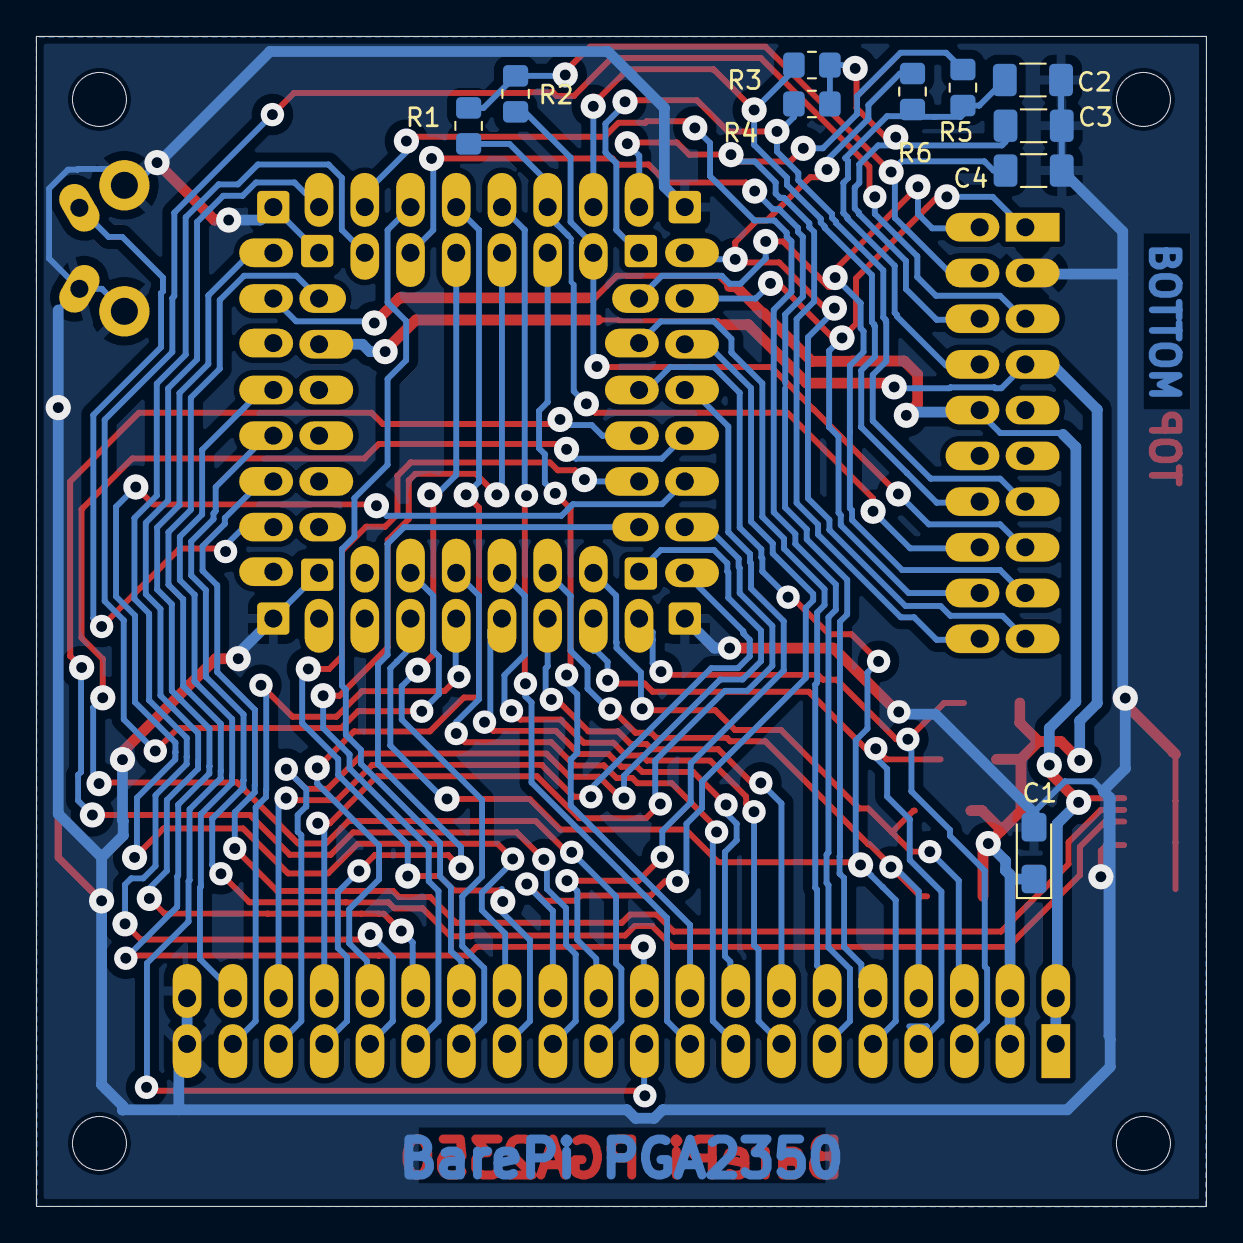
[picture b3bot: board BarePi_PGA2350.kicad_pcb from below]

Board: 2 copper layers, 65.0 x 65.0 mm, 19 parts (10 on the bottom side), 52 nets.

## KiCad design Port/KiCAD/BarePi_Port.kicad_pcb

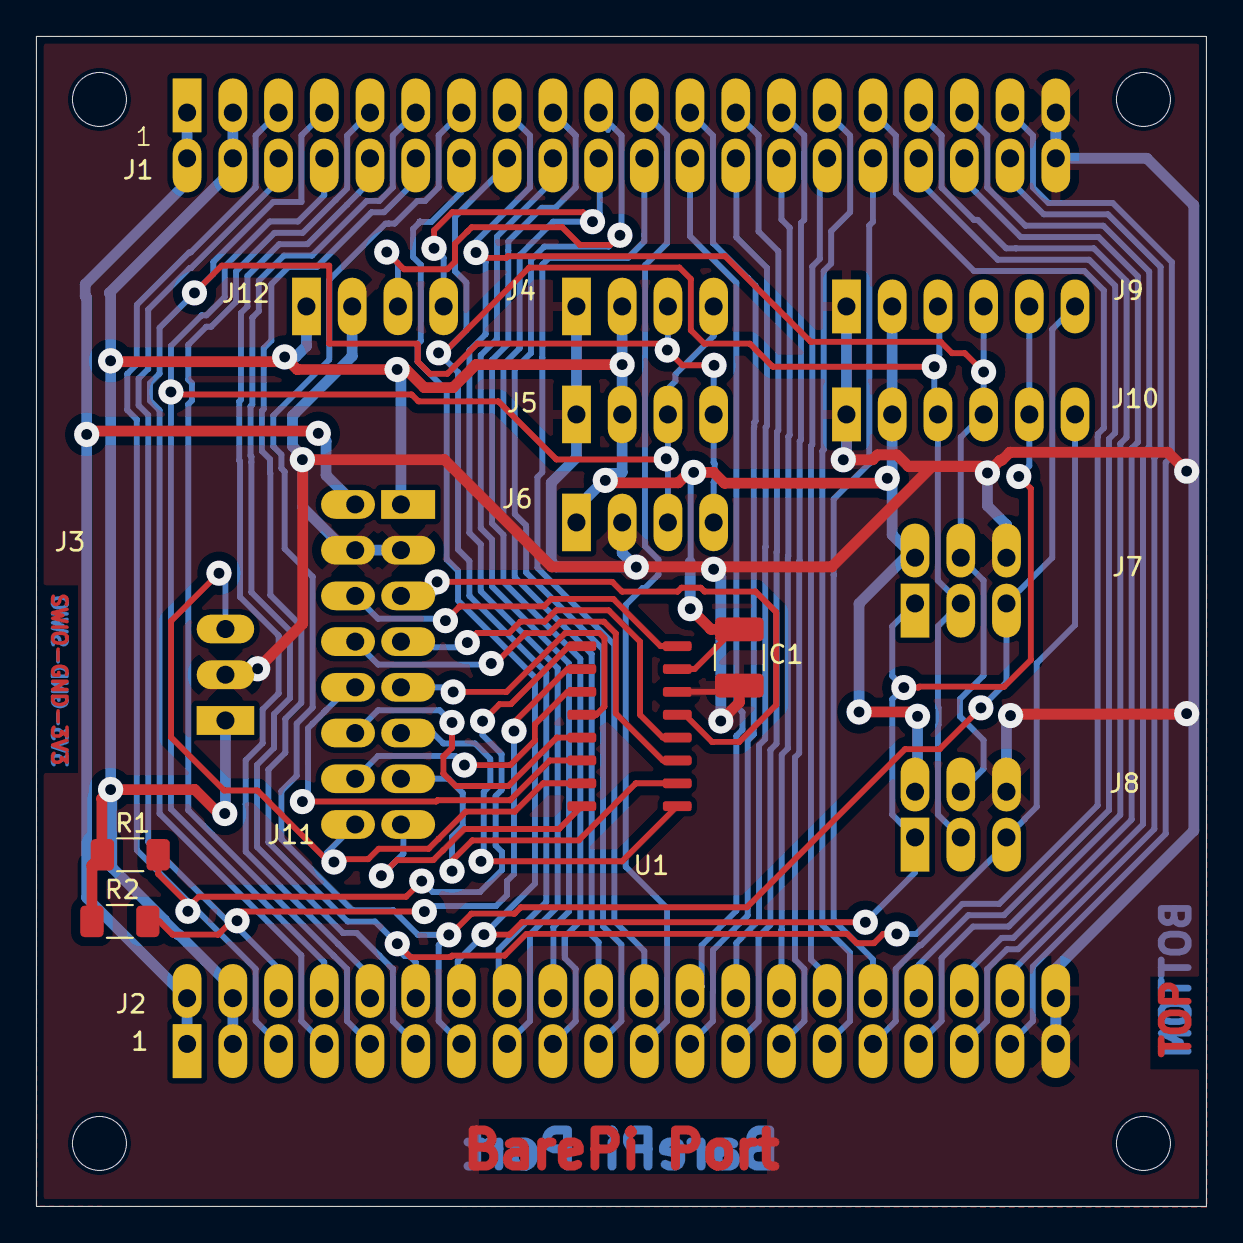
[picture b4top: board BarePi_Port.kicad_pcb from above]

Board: 2 copper layers, 65.0 x 65.0 mm, 16 parts (0 on the bottom side), 49 nets.

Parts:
C1: 100nF; C_1210_3225Metric_Pad1.33x2.70mm_HandSolder
J1: IN; Raspberry_IN_PinHeader_2x20_P2.54mm_Horizontal
J2: OUT; Raspberry_OUT_PinSocket_2x20_P2.54mm_Horizontal
J3: WCH-LINK; Raspberry_PinHeader_1x03_P2.54mm_Horizontal
J4, J5, J6: I2C; Raspberry_PinSocket_1x04_P2.54mm_Vertical
J7: SPI0; Raspberry_IDC-Header_2x03_P2.54mm_Vertical
J8: SPI1; Raspberry_IDC-Header_2x03_P2.54mm_Vertical
J9: SPI0; Raspberry_PinSocket_1x06_P2.54mm_Vertical
J10: SPI1; Raspberry_PinSocket_1x06_P2.54mm_Vertical
J11: PORT; Raspberry_PinSocket_2x08_P2.54mm_Vertical
J12: UART; Raspberry_PinSocket_1x04_P2.54mm_Vertical
R1, R2: 15K; R_1206_3216Metric_Pad1.30x1.75mm_HandSolder
U1: CH32V002A4M6; Raspberry_STC_SOP-16_3.9x9.9mm_P1.27mm

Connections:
/3V3: C1.1, J1.3, J1.4, J2.3, J2.4, J3.1, J4.2, J5.2, J6.1, J7.2, J8.2, J9.2, J10.2, J11.1, J12.1, R1.2, R2.2, U1.15 (VDD)
/5V: J1.1, J1.2, J2.1, J2.2, J11.2
/BUS_SCL: J1.6, J2.6, R2.1, U1.2 (PC2)
/BUS_SDA: J1.5, J2.5, R1.1, U1.1 (PC1)
/GND: C1.2, J1.39, J1.40, J2.39, J2.40, J3.2, J4.1, J5.1, J6.2, J7.6, J8.6, J9.1, J10.1, J11.3, J11.4, J12.2, U1.14 (VSS)
/I2C_SCL: J1.8, J2.8, J4.4, J5.3, J6.3
/I2C_SDA: J1.7, J2.7, J4.3, J5.4, J6.4
/IO0/ADC0: J11.5, U1.13 (PA2/XO/A0)
/IO1/ADC1: J11.7, U1.12 (PA1/XI/A1)
/IO2/ADC2: J11.9, U1.4 (PC4/MCO/A2)
/IO3/ADC3: J11.11, U1.9 (PD5/A5)
/IO4/ADC4: J11.13, U1.10 (PD6/A6)
/IO5/ADC5: J11.15, U1.8 (PD4/A7)
/IO6: J11.6, U1.16 (PC0)
/IO7: J11.8, U1.11 (PD7/RST)
/IO8: J11.10, U1.6 (PC7)
/IO9: J11.12, U1.5 (PC6)
/IO10: J11.14, U1.3 (PC3)
/KEY_A: J1.27, J2.27
/KEY_ALT: J1.9, J2.9
/KEY_B: J1.28, J2.28
/KEY_DOWN: J1.10, J2.10
/KEY_LEFT: J1.31, J2.31
/KEY_RIGHT: J1.30, J2.30
/KEY_UP: J1.11, J2.11
/KEY_X: J1.29, J2.29
/KEY_Y: J1.32, J2.32
/LCD_BL: J1.24, J2.24
/LCD_CS: J1.23, J2.23
/LCD_DC: J1.21, J2.21
/LCD_MOSI: J1.25, J2.25
/LCD_RES: J1.22, J2.22
/LCD_SCK: J1.26, J2.26
/PWM_L: J1.17, J2.17
/PWM_R: J1.18, J2.18
/RESET: J1.38, J2.38
/SD_CS: J1.33, J2.33
/SD_MISO: J1.34, J2.34
/SD_MOSI: J1.35, J2.35
/SD_SCLK: J1.36, J2.36
/SPI_CS0: J1.13, J2.13, J7.5, J9.6
/SPI_CS1: J1.12, J2.12, J8.5, J10.6
/SPI_MISO: J1.14, J2.14, J7.1, J8.1, J9.5, J10.5
/SPI_MOSI: J1.15, J2.15, J7.4, J8.4, J9.4, J10.4
/SPI_SCLK: J1.16, J2.16, J7.3, J8.3, J9.3, J10.3
/SWIO/IO11: J3.3, J11.16, U1.7 (PD1/SWIO)
/UART_RX: J1.20, J2.20, J12.4
/UART_TX: J1.19, J2.19, J12.3
/USR_LED: J1.37, J2.37
